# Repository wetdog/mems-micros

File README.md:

# mems-micros
ICS-43432 mems breakout circular board

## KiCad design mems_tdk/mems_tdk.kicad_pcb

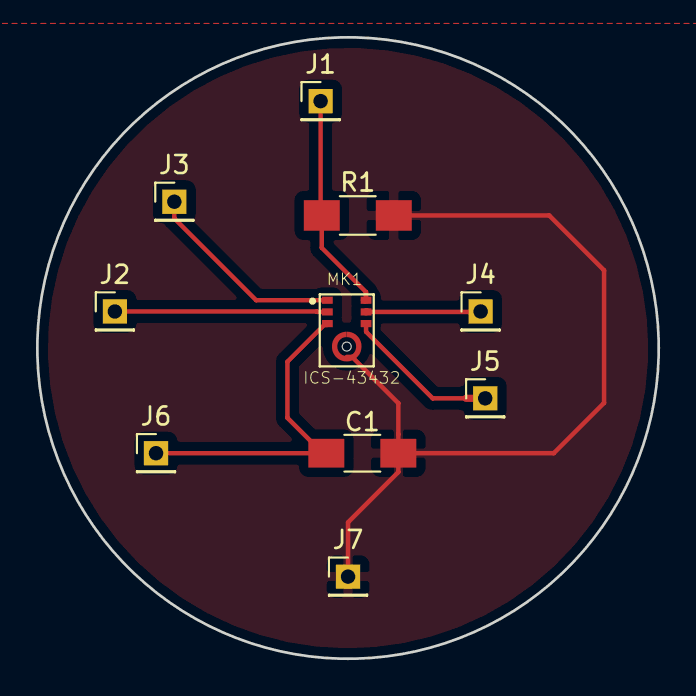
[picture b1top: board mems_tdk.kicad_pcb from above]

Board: 2 copper layers, 34.5 x 34.5 mm, 10 parts (0 on the bottom side), 7 nets.

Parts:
C1: 0.1uF; C_1206_HandSoldering
J1: SD; Pin_Header_Straight_1x01_Pitch2.00mm
J2: CONFIG; Pin_Header_Straight_1x01_Pitch2.00mm
J3: LR; Pin_Header_Straight_1x01_Pitch2.00mm
J4: SCK; Pin_Header_Straight_1x01_Pitch2.00mm
J5: WS; Pin_Header_Straight_1x01_Pitch2.00mm
J6: VCC; Pin_Header_Straight_1x01_Pitch2.00mm
J7: GND; Pin_Header_Straight_1x01_Pitch2.00mm
MK1: ICS-43432; MIC_ICS-43432
R1: 100k; R_1206_HandSoldering

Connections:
GND: C1.2, J7.1, MK1.4, R1.2
unnamed: J1.1, MK1.7, R1.1
unnamed: J2.1, MK1.2
unnamed: J3.1, MK1.1
unnamed: J4.1, MK1.6
unnamed: J5.1, MK1.5
VCC: C1.1, J6.1, MK1.3
